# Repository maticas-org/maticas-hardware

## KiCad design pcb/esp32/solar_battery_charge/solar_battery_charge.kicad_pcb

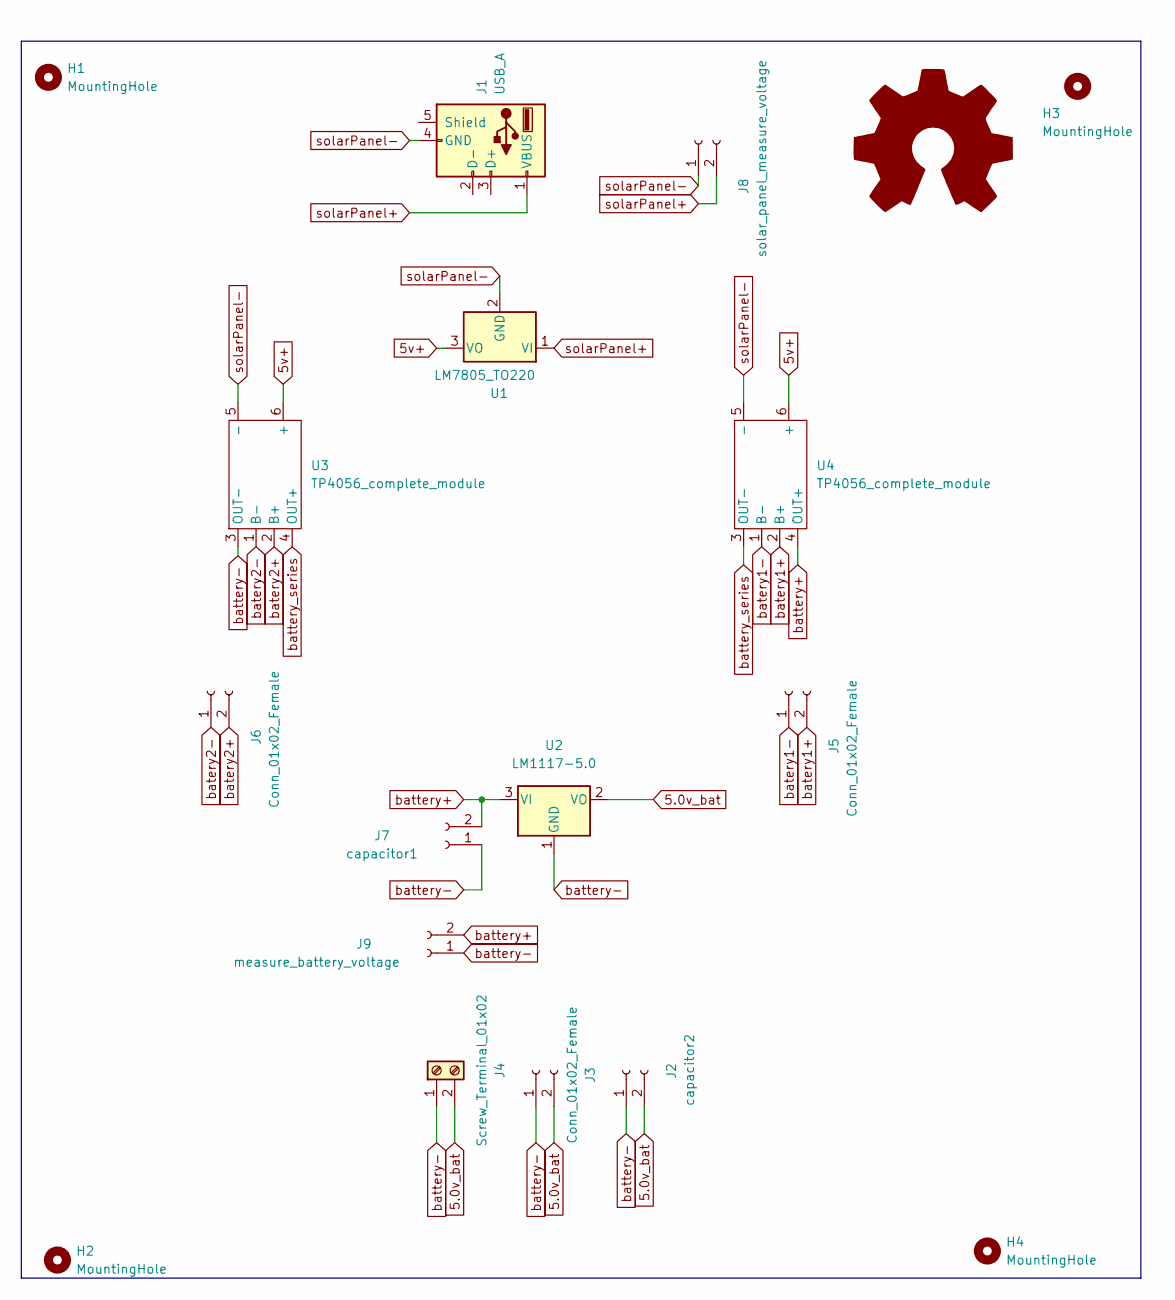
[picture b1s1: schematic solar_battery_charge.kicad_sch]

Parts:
H1, H2, H3, H4: MountingHole; MountingHole_2mm
J1: USB_A; Connector_USB__USB_A_Molex_67643_Horizontal
J2: capacitor2; Connector_Molex_Molex_SL_171971-0004_1x02_P2.54mm_Vertical_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
J3, J5, J6: Conn_01x02_Female; Connector_Molex_Molex_SL_171971-0004_1x02_P2.54mm_Vertical_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
J4: Screw_Terminal_01x02; TerminalBlock__TerminalBlock_bornier-2_P5.08mm
J7: capacitor1; Connector_Molex_Molex_SL_171971-0004_1x02_P2.54mm_Vertical_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
J8: solar_panel_measure_voltage; Connector_Molex_Molex_SL_171971-0004_1x02_P2.54mm_Vertical_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
J9: measure_battery_voltage; Connector_Molex_Molex_SL_171971-0004_1x02_P2.54mm_Vertical_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
U1: LM7805_TO220; Package_TO_SOT_THT__TO-220-3_Vertical_solar_charger
U2: LM1117-5.0; SOT-223-3_TabPin2
U3, U4: TP4056_complete_module; tp4056

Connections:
5.0v_bat: J2.2, J3.2, J4.2, U2.2 (VO)
5v+: U1.3 (VO), U3.6 (+), U4.6 (+)
batery1+: J5.2, U4.2 (B+)
batery1-: J5.1, U4.1 (B-)
batery2+: J6.2, U3.2 (B+)
batery2-: J6.1, U3.1 (B-)
battery+: J7.2, J9.2, U2.3 (VI), U4.4 (OUT+)
battery-: J2.1, J3.1, J4.1, J7.1, J9.1, U2.1 (GND), U3.3 (OUT-)
battery_series: U3.4 (OUT+), U4.3 (OUT-)
solarPanel+: J1.1 (VBUS), J8.2, U1.1 (VI)
solarPanel-: J1.4 (GND), J8.1, U1.2 (GND), U3.5 (-), U4.5 (-)

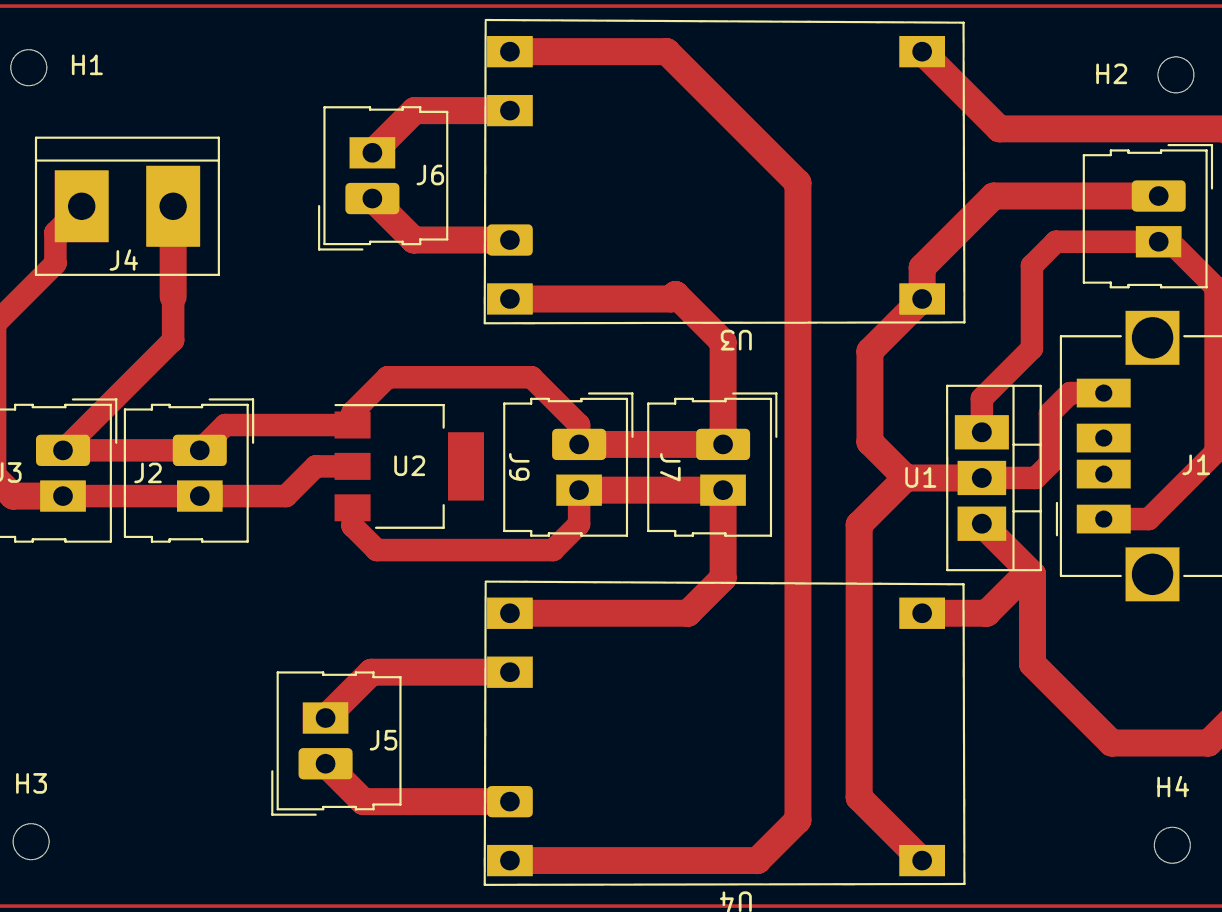
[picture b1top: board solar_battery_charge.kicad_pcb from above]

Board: 2 copper layers, 17 parts (0 on the bottom side), 11 nets.
